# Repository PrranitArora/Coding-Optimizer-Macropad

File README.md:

# Coding-Optimizer-Macropad
There are many key commands I make repetitively while coding that require finger gymnastics. Can optimize this repetitive code by pasting the desired code block by block (on sequential button presses). The blocks are chunked by their ends lining up with the part of the code you need to customize.
Although using a macro pad requires you to leave home-row while writing code, I think the net benefit of not having to write boilerplate code repeatedly greatly outweighs the typing speed reduction. 

# Schematics

# PCB 

# Hackpad Render

# 3D Printed Components

# Main Body

# Lid

# Other Components
Switches (x6): 

Heatset Inserts (x4): 

Screws (x4): 

# Assembled Version (and process demonstration)
Coming Soon!

# Typing speed and coding performance inference testing
Did it really make the coding experience faster? 
Coming Soon!

# Bill of Materials
- 2 SK6812 MINI-E LED (indicator for activated paste sequence) 
- 6 keys
- Uses kmk (may flash qmk later)
- 4 M3x16mm screws
- 4 M3x5mx4mm heatset inserts
- 3D-Printed Case

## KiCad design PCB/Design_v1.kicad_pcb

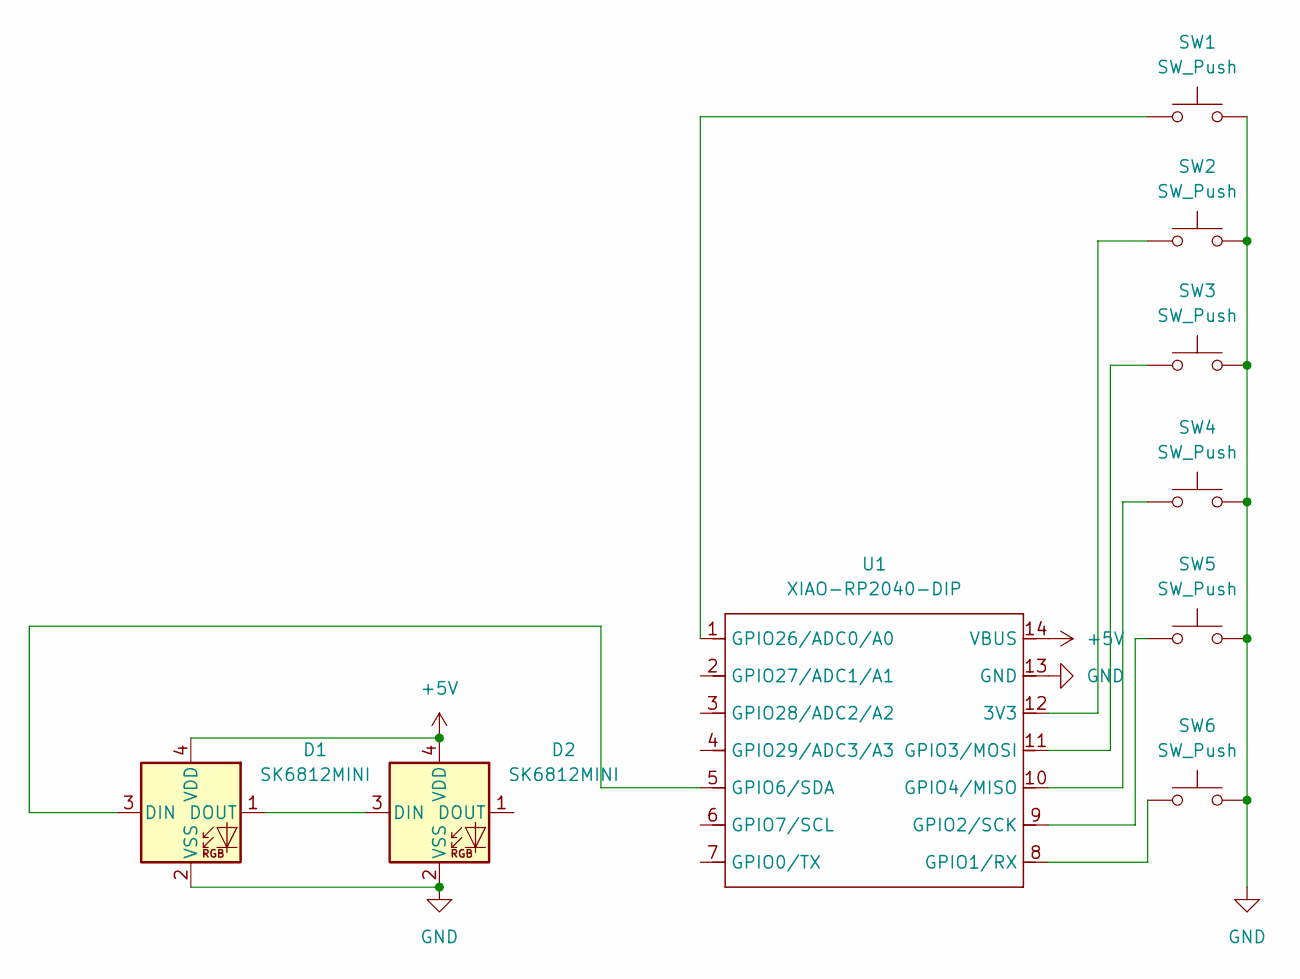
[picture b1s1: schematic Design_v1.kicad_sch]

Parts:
D1, D2: SK6812MINI; LED_SK6812MINI_PLCC4_3.5x3.5mm_P1.75mm
SW1, SW2, SW3, SW4, SW5, SW6: SW_Push; SW_Cherry_MX_1.00u_PCB
U1: XIAO-RP2040-DIP

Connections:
+5V: D1.4 (VDD), D2.4 (VDD), U1.14 (VBUS)
GND: D1.2 (VSS), D2.2 (VSS), SW1.2, SW2.2, SW3.2, SW4.2, SW5.2, SW6.2, U1.13 (GND)
unnamed: D1.3 (DIN), U1.5 (GPIO6/SDA)
unnamed: D1.1 (DOUT), D2.3 (DIN)
unnamed: SW2.1, U1.12 (3V3)
unnamed: SW6.1, U1.8 (GPIO1/RX)
unnamed: SW5.1, U1.9 (GPIO2/SCK)
unnamed: SW3.1, U1.11 (GPIO3/MOSI)
unnamed: SW4.1, U1.10 (GPIO4/MISO)
unnamed: SW1.1, U1.1 (GPIO26/ADC0/A0)

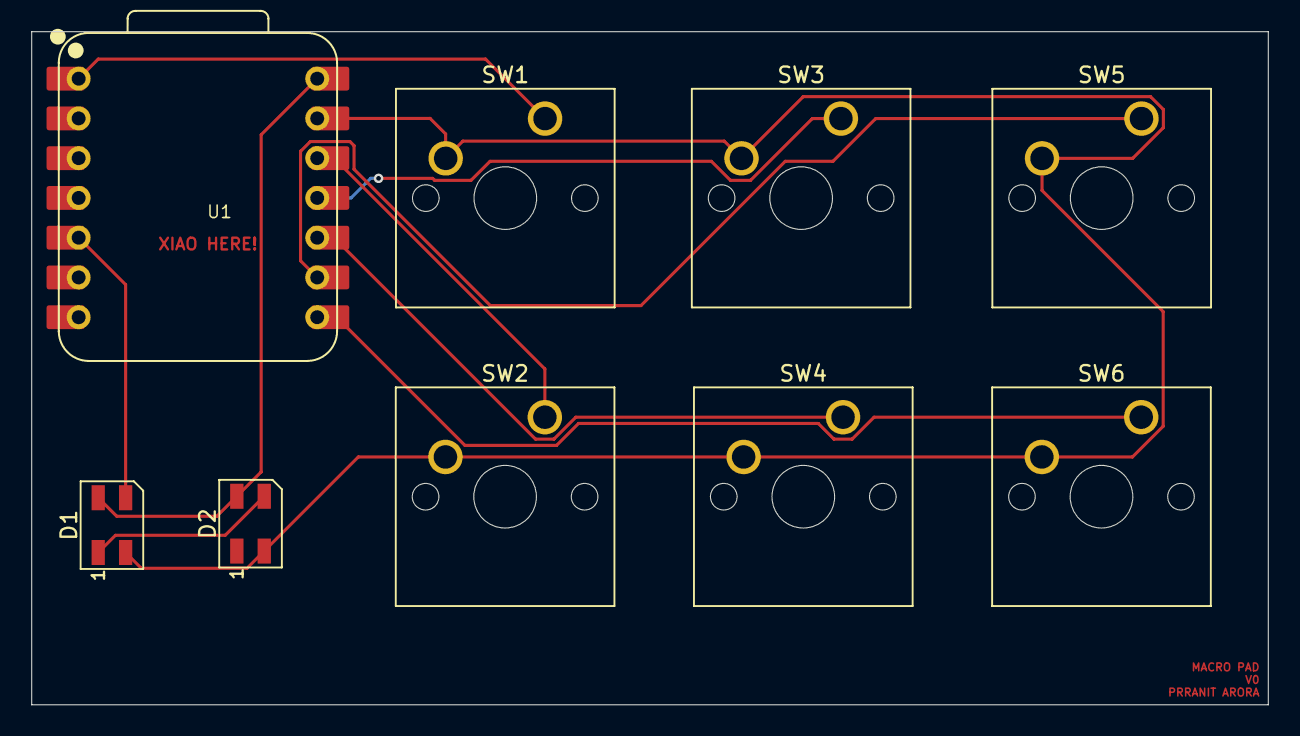
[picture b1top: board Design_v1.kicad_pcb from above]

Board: 2 copper layers, 79.0 x 43.0 mm, 9 parts (0 on the bottom side), 10 nets.

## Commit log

2025-12-04 Revise features in README
    Updated features list to reflect changes in LED count and firmware.
2025-12-04 upload main design files
2025-12-04 Visualizations for README
    Added schematics, PCB, and component images to README.
2025-12-04 Update README with PCB Render
    Added sections on typing speed testing and bill of materials.
2025-12-04 Add additional images to README.md
